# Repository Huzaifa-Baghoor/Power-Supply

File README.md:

# Discreete Dual Output DC Power Supply
This is a Custom Designed dual output DC power supply that provides 12V and 5V outputs.

## Working
The circuit takes AC input from Wall Socket and steps it down to 12V then this AC voltage is rectified be 1N4007 Diodes. This 12V DC voltage then goes to a capacitor which decreases the noise and the voltage goes to about 17V. then this voltage is passed through capacitors and zener diodes to provide the 12V and 5V outputs.

## Simulation
This Project is Simulated and Tested in Multisim. It worked fine there and supplied constant voltage under Load.

## PCB and Connections
I designed a Custom PCB for this project.

|Schematics|Tracks|
| :---: | :---: |
|  |  |

## 3D Case

I also designed a 3D enclosure box for the project that would have 3 holes, 1 for input and 2 for the outputs.
|Schematics|Tracks|
| :---: | :---: |
|  |  |

## BOM

| Name | Purpose | Quantity | Total Cost (USD) | Link | Distributor |
| :---: | :---: | :---: | :---: | :---: | :---: |
| Transperency sheets | Printing PCB design | 1 | 8 | [Transperency sheets](https://stationers.pk/products/transparency-sheets?srsltid=AfmBOoo0qg_GjBXsgpL0SoCESp01tAI8nJvPUPbaVxZx4DztRgOZabL1) | Stationers |
| Copper Clad Board | Making PCB | 1 | 7 | [Copper Clad Board](https://epro.pk/product/double-sided-pcb-12x12-in-pakistan/) | Epro |
| Capacitors | Reducing Noise | 1 | 5 | https://a.aliexpress.com/_c4OXuY5T | AliExpress |
| Resistor | Resistance | 4 | 8 | [Resistor](https://www.aliexpress.com/item/1005006898731441.html?spm=a2g0o.productlist.main.2.5adb174e6BrR4E&algo_pvid=a8b488c6-4e8d-4539-8e68-136df8322c2e&algo_exp_id=a8b488c6-4e8d-4539-8e68-136df8322c2e-1&pdp_ext_f=%7B%22order%22%3A%2218454%22%2C%22spu_best_type%22%3A%22price%22%2C%22eval%22%3A%221%22%2C%22fromPage%22%3A%22search%22%7D&pdp_npi=6%40dis%21PKR%21700.27%21540.04%21%21%2115.19%2111.71%21%40213ba0c517805536286016955e1c85%2112000038655131992%21sea%21PK%212961473668%21X%211%210%21n_tag%3A-29919%3Bd%3A7347b7cd%3Bm03_new_user%3A-29895%3BpisId%3A5000000208499468&curPageLogUid=xK5nH0KMlH7Z&utparam-url=scene%3Asearch%7Cquery_from%3A%7Cx_object_id%3A1005006898731441%7C_p_origin_prod%3A) | AliExpress |
| 12v Transformer | Stepping Down 220V to 12V | 1 | 7 | [12v Transformer](https://www.aliexpress.com/item/1005002190993881.html?spm=a2g0o.productlist.main.3.5ab7c57cYfLk9E&algo_pvid=73899792-524f-4ba5-b0be-0d52e075c67c&algo_exp_id=73899792-524f-4ba5-b0be-0d52e075c67c-2&pdp_ext_f=%7B%22order%22%3A%2269%22%2C%22spu_best_type%22%3A%22price%22%2C%22eval%22%3A%221%22%2C%22fromPage%22%3A%22search%22%7D&pdp_npi=6%40dis%21PKR%212058.51%211933.56%21%21%216.59%216.19%21%40212e520d17805533749515631efcd4%2112000019002828064%21sea%21PK%212961473668%21X%211%210%21n_tag%3A-29919%3Bd%3A7347b7cd%3Bm03_new_user%3A-29895&curPageLogUid=AV8pa8Zxzb4a&utparam-url=scene%3Asearch%7Cquery_from%3A%7Cx_object_id%3A1005002190993881%7C_p_origin_prod%3A) | AliExpress |
| 1n5407 | Diode | 1 | 5.9 | [1n5407](https://www.aliexpress.com/item/1005005485365222.html?spm=a2g0o.productlist.main.1.368665a2Kra7P6&algo_pvid=32606de9-9aea-4d42-ae9b-a578256993a0&algo_exp_id=32606de9-9aea-4d42-ae9b-a578256993a0-0&pdp_ext_f=%7B%22order%22%3A%2254%22%2C%22eval%22%3A%221%22%2C%22fromPage%22%3A%22search%22%7D&pdp_npi=6%40dis%21PKR%211917.94%211568.09%21%21%216.14%215.02%21%402151e6dc17805527475088759e359e%2112000033269855528%21sea%21PK%210%21ABX%211%210%21n_tag%3A-29910%3Bd%3A7347b7cd%3Bm03_new_user%3A-29895%3BpisId%3A5000000203713833&curPageLogUid=w31Z33jQx7jN&utparam-url=scene%3Asearch%7Cquery_from%3A%7Cx_object_id%3A1005005485365222%7C_p_origin_prod%3A) | AliExpress |
| Diode | Rectifier | 1 | 3.6 | [Diode](https://www.aliexpress.com/item/1005012369097375.html?spm=a2g0o.productlist.main.3.e8886f76qmjBun&algo_pvid=c9794048-4184-407d-bd0b-0edbe400970a&algo_exp_id=c9794048-4184-407d-bd0b-0edbe400970a-2&pdp_ext_f=%7B%22order%22%3A%221%22%2C%22eval%22%3A%221%22%2C%22fromPage%22%3A%22search%22%7D&pdp_npi=6%40dis%21PKR%213746.13%211045.14%21%21%2181.26%2122.67%21%40212a70c017805519689011413e223e%2112000058193885987%21sea%21PK%210%21ABX%211%210%21n_tag%3A-29910%3Bd%3A7347b7cd%3Bm03_new_user%3A-29895%3BpisId%3A5000000208221885&curPageLogUid=psqZq8pejmBE&utparam-url=scene%3Asearch%7Cquery_from%3A%7Cx_object_id%3A1005012369097375%7C_p_origin_prod%3A) | AliExpress |

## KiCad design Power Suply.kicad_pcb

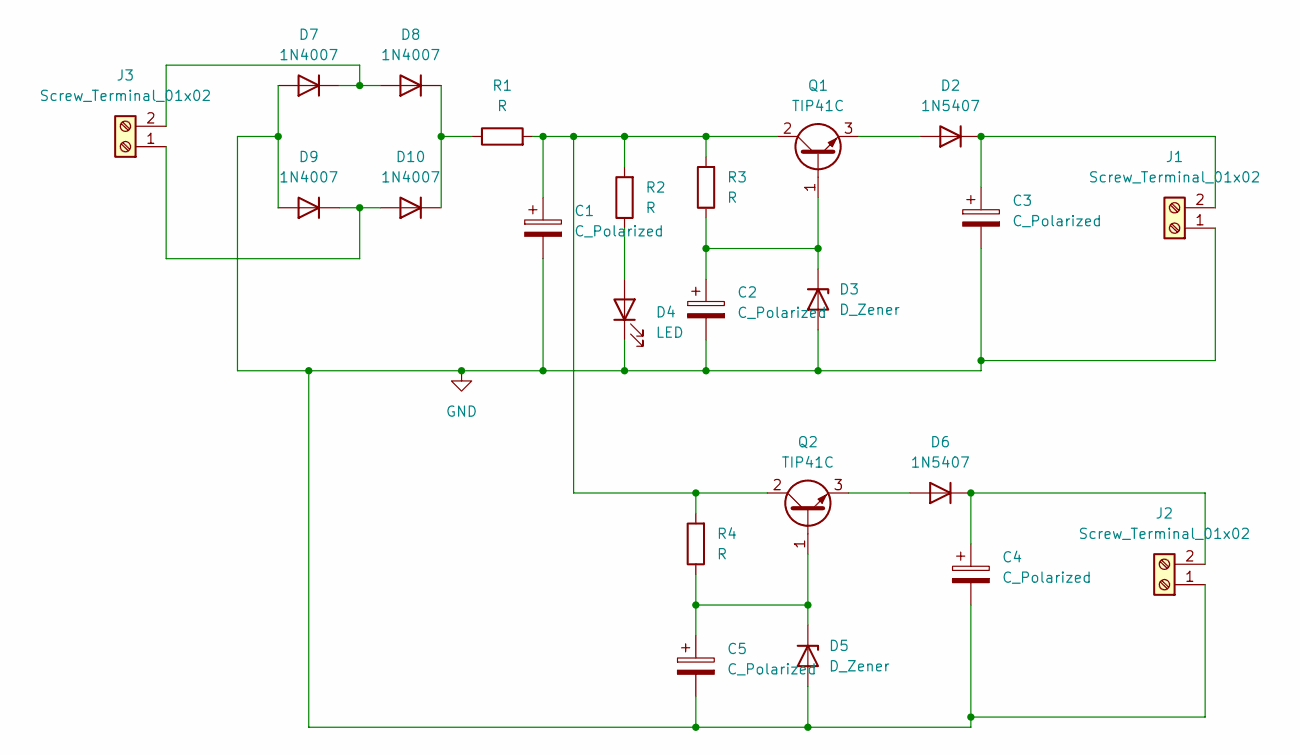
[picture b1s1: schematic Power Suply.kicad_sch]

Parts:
C1, C2, C3, C4, C5: C_Polarized; CP_Radial_D10.0mm_P5.00mm
D2, D6: 1N5407; D_DO-41_SOD81_P10.16mm_Horizontal
D3, D5: D_Zener; D_DO-41_SOD81_P10.16mm_Horizontal
D4: LED; LED_D5.0mm
D7, D8, D9, D10: 1N4007; D_DO-41_SOD81_P10.16mm_Horizontal
J1, J2, J3: Screw_Terminal_01x02; TerminalBlock_Phoenix_MKDS-1,5-2-5.08_1x02_P5.08mm_Horizont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
Q1, Q2: TIP41C; TO-220-3_Vertical
R1, R2, R3, R4: R; R_Axial_DIN0207_L6.3mm_D2.5mm_P7.62mm_Horizontal

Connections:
GND: C1.2, C2.2, C3.2, C4.2, C5.2, D3.2 (A), D4.1 (K), D5.2 (A), D7.2 (A), D9.2 (A), J1.1, J2.1
unnamed: D2.2 (A), Q1.3 (E)
unnamed: C3.1, D2.1 (K), J1.2
unnamed: C2.1, D3.1 (K), Q1.1 (B), R3.1
unnamed: D4.2 (A), R2.1
unnamed: C5.1, D5.1 (K), Q2.1 (B), R4.1
unnamed: D6.2 (A), Q2.3 (E)
unnamed: C4.1, D6.1 (K), J2.2
unnamed: D7.1 (K), D8.2 (A), J3.2
unnamed: D9.1 (K), D10.2 (A), J3.1
unnamed: D8.1 (K), D10.1 (K), R1.1
unnamed: C1.1, Q1.2 (C), Q2.2 (C), R1.2, R2.2, R3.2, R4.2

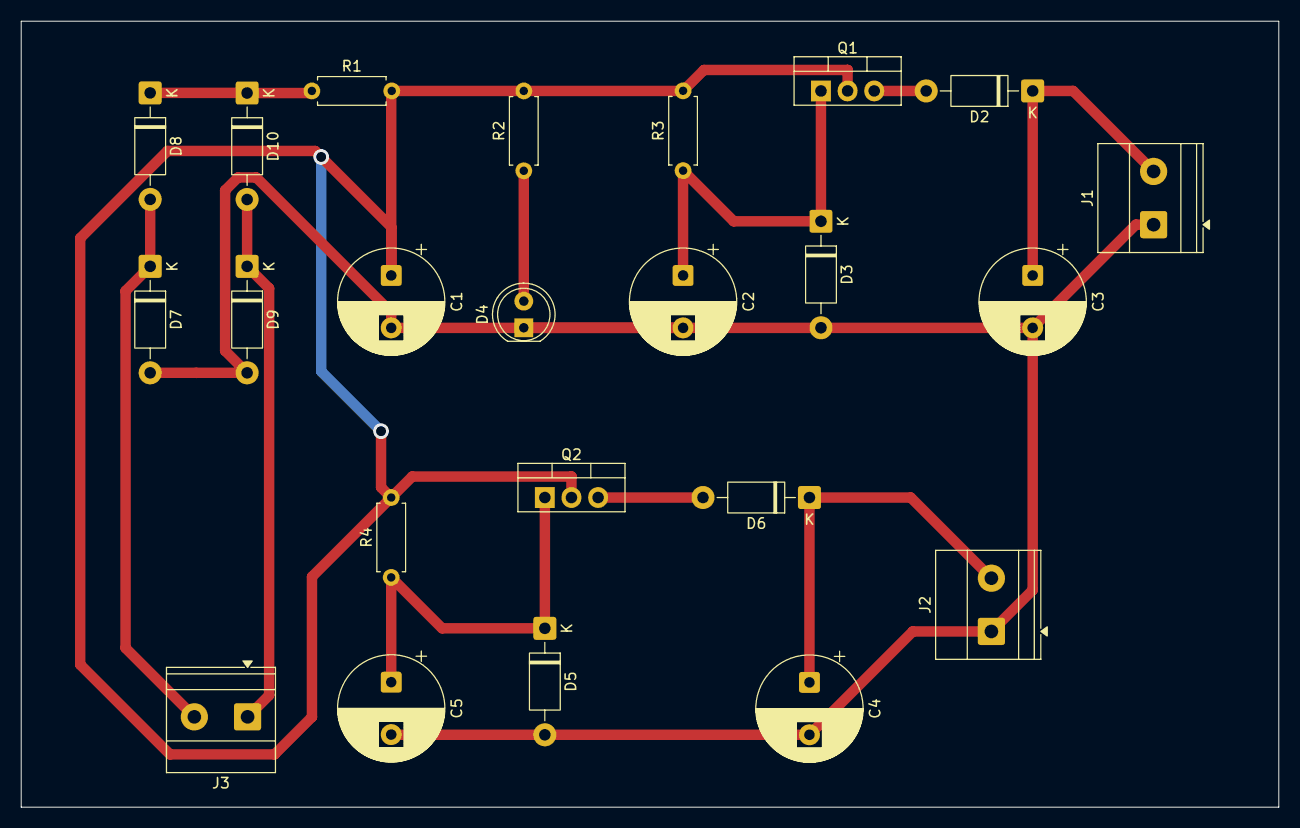
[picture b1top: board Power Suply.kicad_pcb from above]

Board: 2 copper layers, 120.0 x 75.0 mm, 23 parts (0 on the bottom side), 12 nets.

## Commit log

2026-05-17 PCB v1
2026-06-04 Readme
2026-06-04 Images
2026-06-04 images in readme
2026-06-04 Restructuring
2026-06-14 Added 3D Files
2026-06-15 Add link for capacitors in README materials list
    Added link for capacitors in the materials table.
2026-06-15 Modify capacitors entry in components list
    Updated the quantity and cost of capacitors in the components list.
2026-06-30 Added project image
2026-06-30 Change image reference in README
    Updated image reference in README from 3D.JPG to IMG_20260629_234208_990.jpg.
